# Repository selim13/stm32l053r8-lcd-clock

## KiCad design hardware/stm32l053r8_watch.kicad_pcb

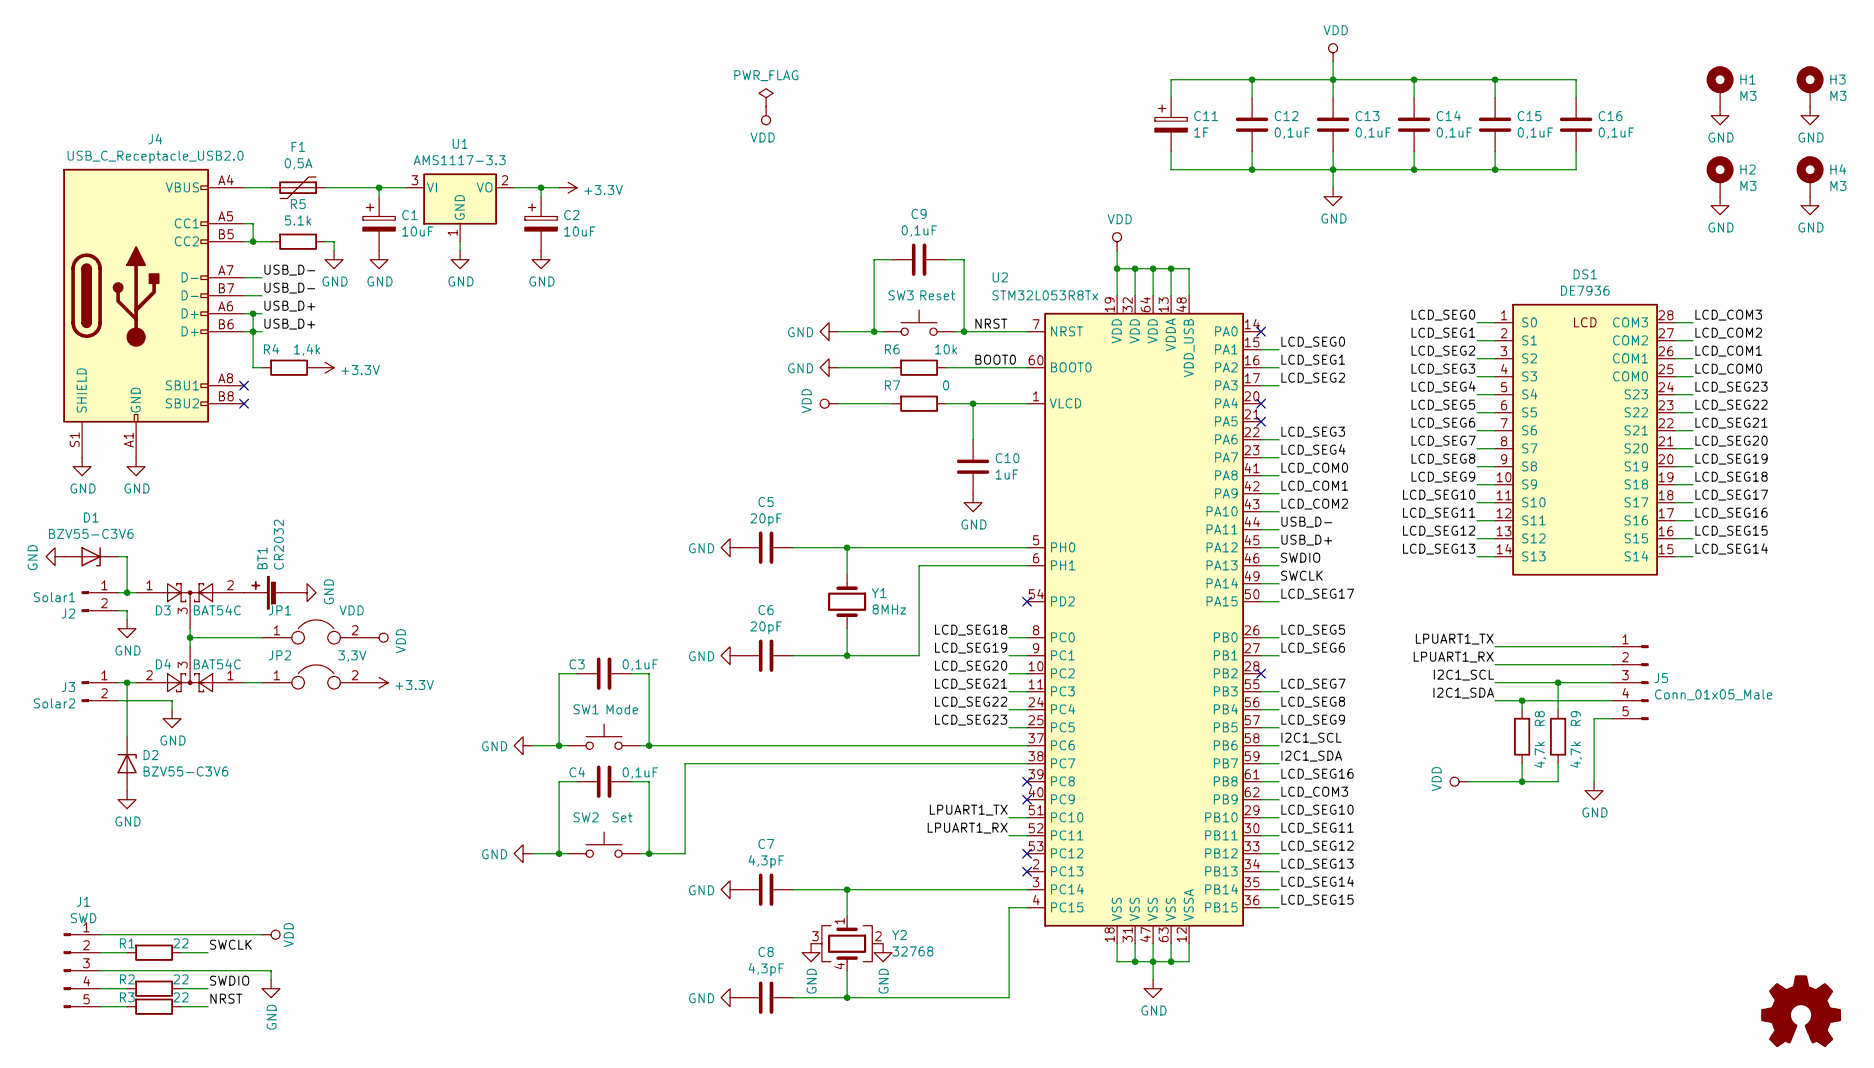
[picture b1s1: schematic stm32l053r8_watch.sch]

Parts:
BT1: CR2032; BatteryHolder_1x2032
C1, C2: 10uF; CP_EIA-3216-18_Kemet-A
C3, C4, C9, C12, C13, C14, C15, C16: 0,1uF; C_0805_2012Metric
C5, C6: 20pF; C_0805_2012Metric
C7, C8: 4,3pF; C_0805_2012Metric
C10: 1uF; C_0805_2012Metric
C11: 1F; CP_Radial_D21.0mm_P5.00mm
D1, D2: BZV55-C3V6; D_MiniMELF
D3, D4: BAT54C; SOT-23
DS1: DE7936
F1: 0,5A; Fuse_1812_4532Metric
H1, H2, H3, H4: M3; MountingHole_3.2mm_M3_Pad_Via
J1: SWD; PinHeader_1x05_P2.54mm_Vertical
J2: Solar1; JST_PH_B2B-PH-K_1x02_P2.00mm_Vertical
J3: Solar2; JST_PH_B2B-PH-K_1x02_P2.00mm_Vertical
J4: USB_C_Receptacle_USB2.0; USB_C_Receptacle_USB2.0_16P
J5: Conn_01x05_Male; PinHeader_1x05_P2.54mm_Vertical
JP1: VDD; SolderJumper-2_P1.3mm_Bridged2Bar_Pad1.0x1.5mm
JP2: 3,3V; SolderJumper-2_P1.3mm_Bridged2Bar_Pad1.0x1.5mm
R1, R2, R3: 22; R_0805_2012Metric
R4: 1,4k; R_0805_2012Metric
R5: 5.1k; R_0805_2012Metric
R6: 10k; R_0805_2012Metric
R7: 0; R_0805_2012Metric
R8, R9: 4,7k; R_0805_2012Metric
SW1: Mode; SW_PUSH_6mm_H9.5mm
SW2: Set; SW_PUSH_6mm_H9.5mm
SW3: Reset; SW_PUSH_6mm
U1: AMS1117-3.3; SOT-223-3_TabPin2
U2: STM32L053R8Tx; LQFP-64_10x10mm_P0.5mm
Y1: 8MHz; Crystal_SMD_HC49-SD
Y2: 32768; Crystal_SMD_SeikoEpson_MC406-4Pin_9.6x4.1mm

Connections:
+3V3: C2.1, JP2.2, R4.1, U1.2 (VO)
/BOOT0: R6.1, U2.60 (BOOT0)
/I2C1_SCL: J5.3, R9.2, U2.58 (PB6)
/I2C1_SDA: J5.4, R8.2, U2.59 (PB7)
/LCD_COM0: DS1.25 (COM0), U2.41 (PA8)
/LCD_COM1: DS1.26 (COM1), U2.42 (PA9)
/LCD_COM2: DS1.27 (COM2), U2.43 (PA10)
/LCD_COM3: DS1.28 (COM3), U2.62 (PB9)
/LCD_SEG0: DS1.1 (S0), U2.15 (PA1)
/LCD_SEG1: DS1.2 (S1), U2.16 (PA2)
/LCD_SEG2: DS1.3 (S2), U2.17 (PA3)
/LCD_SEG3: DS1.4 (S3), U2.22 (PA6)
/LCD_SEG4: DS1.5 (S4), U2.23 (PA7)
/LCD_SEG5: DS1.6 (S5), U2.26 (PB0)
/LCD_SEG6: DS1.7 (S6), U2.27 (PB1)
/LCD_SEG7: DS1.8 (S7), U2.55 (PB3)
/LCD_SEG8: DS1.9 (S8), U2.56 (PB4)
/LCD_SEG9: DS1.10 (S9), U2.57 (PB5)
/LCD_SEG10: DS1.11 (S10), U2.29 (PB10)
/LCD_SEG11: DS1.12 (S11), U2.30 (PB11)
/LCD_SEG12: DS1.13 (S12), U2.33 (PB12)
/LCD_SEG13: DS1.14 (S13), U2.34 (PB13)
/LCD_SEG14: DS1.15 (S14), U2.35 (PB14)
/LCD_SEG15: DS1.16 (S15), U2.36 (PB15)
/LCD_SEG16: DS1.17 (S16), U2.61 (PB8)
/LCD_SEG17: DS1.18 (S17), U2.50 (PA15)
/LCD_SEG18: DS1.19 (S18), U2.8 (PC0)
/LCD_SEG19: DS1.20 (S19), U2.9 (PC1)
/LCD_SEG20: DS1.21 (S20), U2.10 (PC2)
/LCD_SEG21: DS1.22 (S21), U2.11 (PC3)
/LCD_SEG22: DS1.23 (S22), U2.24 (PC4)
/LCD_SEG23: DS1.24 (S23), U2.25 (PC5)
/LPUART1_RX: J5.1, U2.51 (PC10)
/LPUART1_TX: J5.2, U2.52 (PC11)
/NRST: C9.2, R3.1, SW3.2, U2.7 (NRST)
/SWCLK: R1.1, U2.49 (PA14)
/SWDIO: R2.1, U2.46 (PA13)
/USB_D+: J4.A6 (D+), J4.B6 (D+), R4.2, U2.45 (PA12)
/USB_D-: J4.A7 (D-), J4.B7 (D-), U2.44 (PA11)
GND: BT1.2 (-), C1.2, C2.2, C3.1, C4.1, C5.2, C6.2, C7.2, C8.2, C9.1, C10.1, C11.2, C12.1, C13.1, C14.1, C15.1, C16.1, D1.2 (A), D2.2 (A), H1.1, H2.1, H3.1, H4.1, J1.3, J2.2, J3.2, J4.A1 (GND), J4.A12 (GND), J4.B1 (GND), J4.B12 (GND), J4.S1 (SHIELD), J5.5, R5.1, R6.2, SW1.1, SW2.1, SW3.1, U1.1 (GND), U2.12 (VSSA), U2.18 (VSS), U2.31 (VSS), U2.47 (VSS), U2.63 (VSS), Y2.2, Y2.3
unnamed: BT1.1 (+), D3.2
unnamed: C1.1, F1.1, U1.3 (VI)
unnamed: C3.2, SW1.2, U2.37 (PC6)
unnamed: C4.2, SW2.2, U2.38 (PC7)
unnamed: C5.1, U2.5 (PH0), Y1.1
unnamed: C6.1, U2.6 (PH1), Y1.2
unnamed: C7.1, U2.3 (PC14), Y2.1
unnamed: C8.1, U2.4 (PC15), Y2.4
unnamed: C10.2, R7.1, U2.1 (VLCD)
unnamed: D1.1 (K), D3.1, J2.1
unnamed: D2.1 (K), D4.2, J3.1
unnamed: D3.3, D4.3, JP1.1
unnamed: D4.1, JP2.1
unnamed: F1.2, J4.A4 (VBUS), J4.A9 (VBUS), J4.B4 (VBUS), J4.B9 (VBUS)
unnamed: J1.2, R1.2
unnamed: J1.4, R2.2
unnamed: J1.5, R3.2
unnamed: J4.A5 (CC1), J4.B5 (CC2), R5.2
VDD: C11.1, C12.2, C13.2, C14.2, C15.2, C16.2, J1.1, JP1.2, R7.2, R8.1, R9.1, U2.13 (VDDA), U2.19 (VDD), U2.32 (VDD), U2.48 (VDD_USB), U2.64 (VDD)

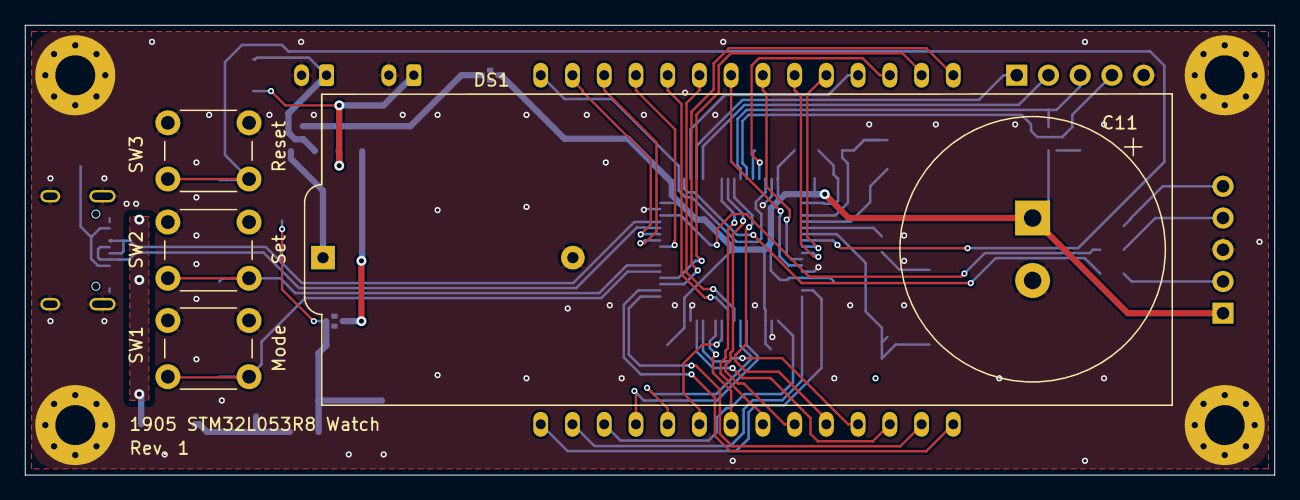
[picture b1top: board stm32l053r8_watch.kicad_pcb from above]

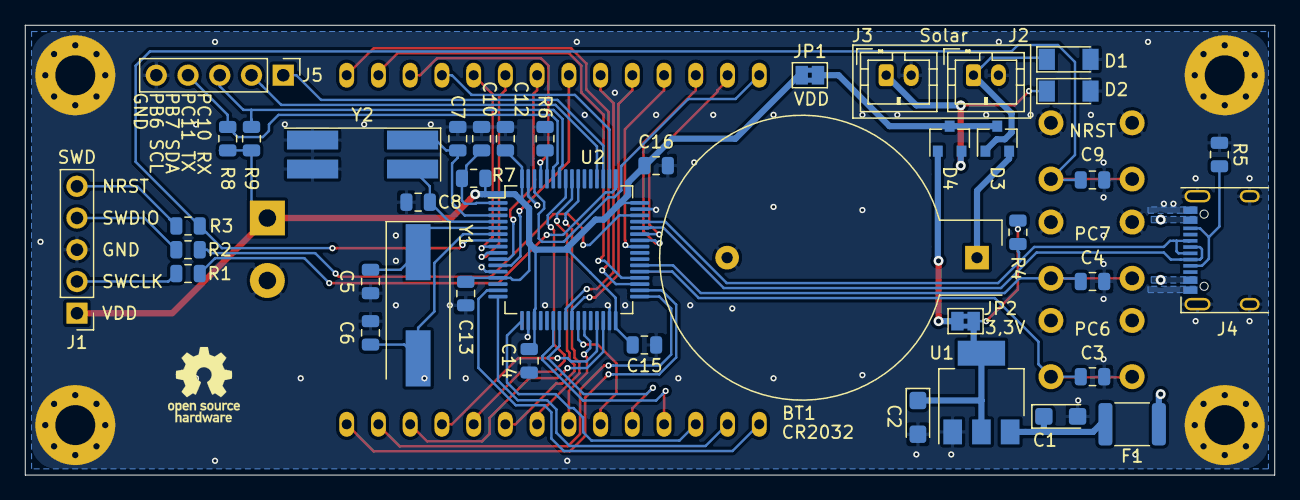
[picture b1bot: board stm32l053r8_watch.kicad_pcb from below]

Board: 2 copper layers, 100.0 x 36.0 mm, 50 parts (41 on the bottom side), 59 nets.

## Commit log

2019-07-07 initia commit
2019-07-07 add vscode stuff
2021-08-25 refactor stuff
